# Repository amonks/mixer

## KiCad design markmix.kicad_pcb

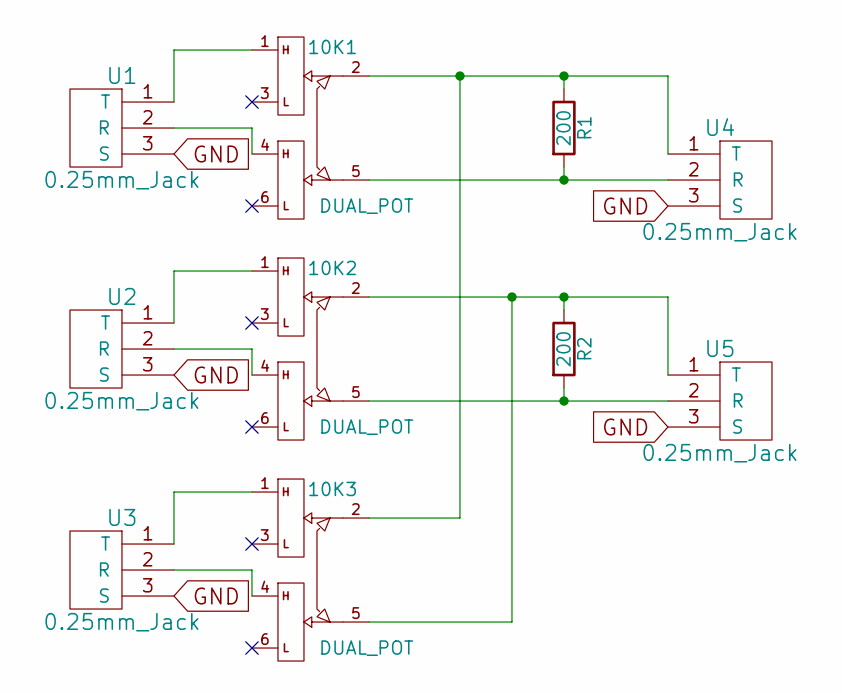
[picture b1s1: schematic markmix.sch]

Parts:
10K1, 10K2, 10K3: DUAL_POT; alps-dual-gang-vertical-pot-RK12L12C0A0G
R1, R2: 200; Resistor_Horizontal_RM10mm
U1, U2, U3, U4, U5: 0.25mm_Jack; 0.25-jack

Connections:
GND: U1.3 (S), U2.3 (S), U3.3 (S), U4.3 (S), U5.3 (S)
unnamed: 10K1.1, U1.1 (T)
unnamed: 10K1.2, 10K3.2, R1.1, U4.1 (T)
unnamed: 10K1.4, U1.2 (R)
unnamed: 10K1.5, R1.2, U4.2 (R)
unnamed: 10K2.1, U2.1 (T)
unnamed: 10K2.2, 10K3.5, R2.1, U5.1 (T)
unnamed: 10K2.4, U2.2 (R)
unnamed: 10K2.5, R2.2, U5.2 (R)
unnamed: 10K3.1, U3.1 (T)
unnamed: 10K3.4, U3.2 (R)

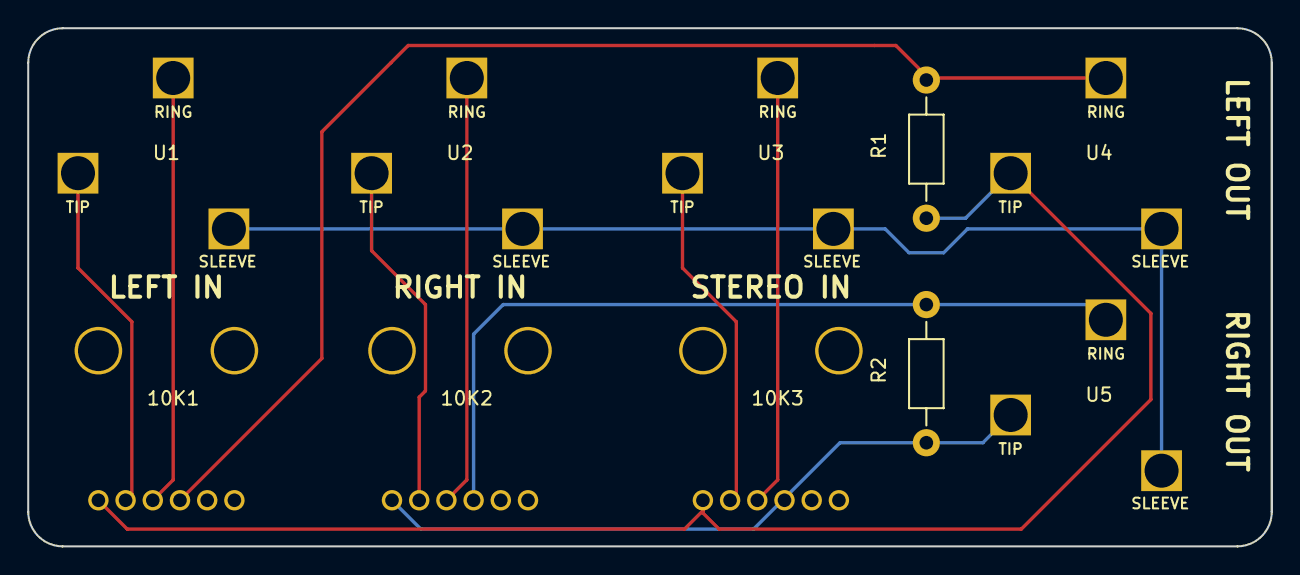
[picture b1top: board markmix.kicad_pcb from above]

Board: 2 copper layers, 91.4 x 38.1 mm, 10 parts (0 on the bottom side), 11 nets.
